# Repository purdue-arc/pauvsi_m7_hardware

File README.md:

# Mission-7-Triggering-System
The system which triggers the ground robots

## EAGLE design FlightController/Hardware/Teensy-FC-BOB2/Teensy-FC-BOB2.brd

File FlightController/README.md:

# Mission-7-Flight-Controller
This repository holds the pcb design and code for the flight controller

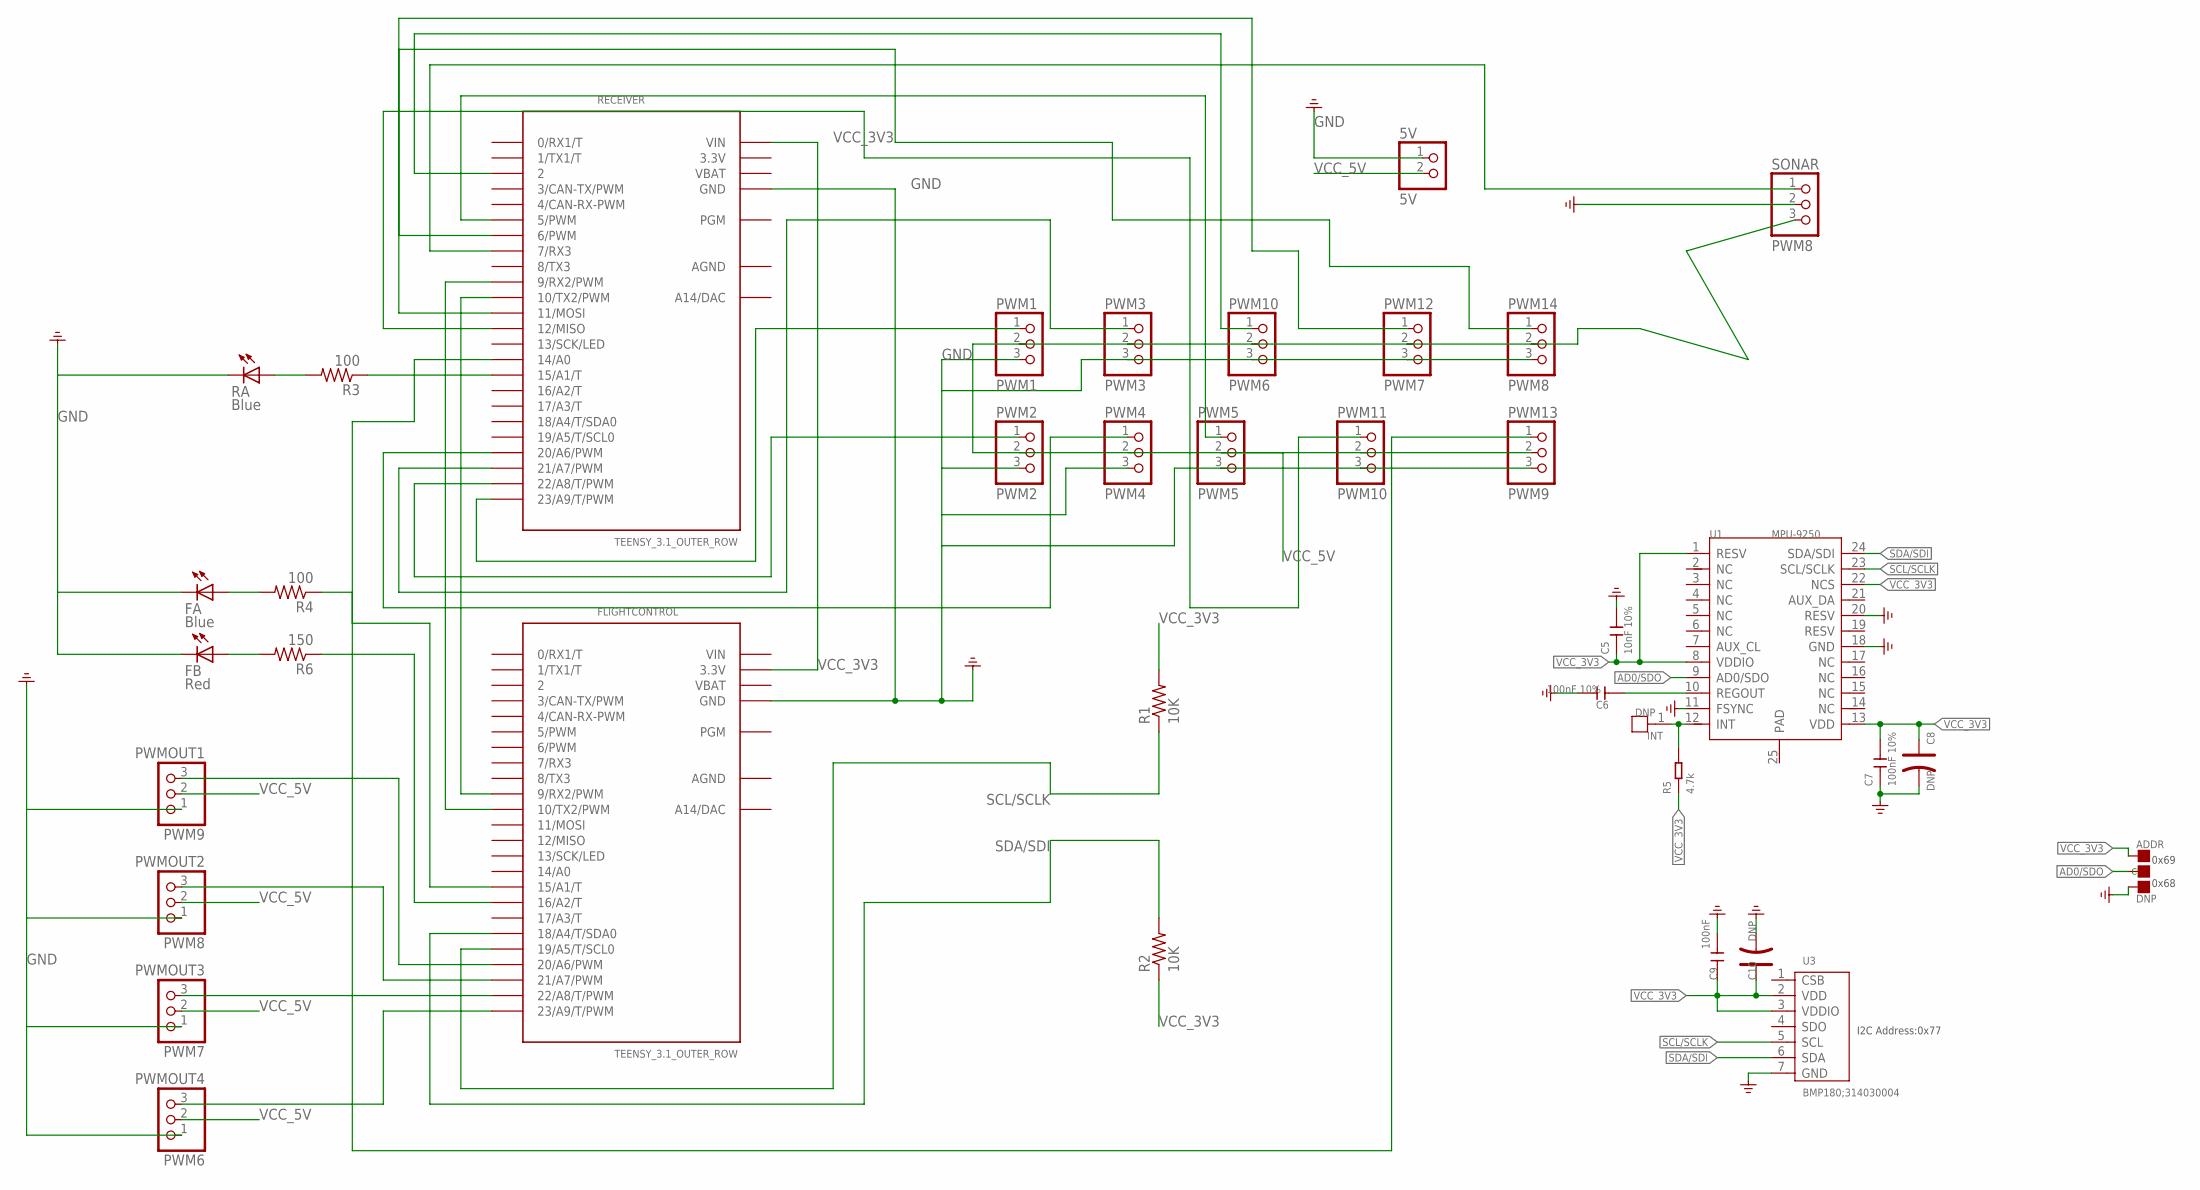
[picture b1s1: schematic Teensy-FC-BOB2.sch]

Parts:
5V: 5V; 1X02
ADDR: DNP; 3P-SMD-L4.1*W1.5MM
C5: 10nF 10%; C0603
C6, C7: 100nF 10%; C0603
C8, C10: DNP; AVX-A
C9: 100nF; C0603
FA: Blue; CHIP-LED0603
FB: Red; CHIP-LED0603
FLIGHTCONTROL: TEENSY_3.1_OUTER_ROW; TEENSY3-OUTER_ROW
INT: DNP; 1P-65/35MIL
PWM1: PWM1; 1X03
PWM2: PWM2; 1X03
PWM3: PWM3; 1X03
PWM4: PWM4; 1X03
PWM5: PWM5; 1X03
PWM6: PWMOUT4; 1X03
PWM7: PWMOUT3; 1X03
PWM8: PWMOUT2; 1X03
PWM9: PWMOUT1; 1X03
PWM10: PWM6; 1X03
PWM11: PWM10; 1X03
PWM12: PWM7; 1X03
PWM13: PWM9; 1X03
PWM14: PWM8; 1X03
R1, R2: 10K; R0603
R3, R4: 100; R0603
R5: 4.7k; R0603
R6: 150; R0603
RA: Blue; CHIP-LED0603
RECEIVER: TEENSY_3.1_OUTER_ROW; TEENSY3-OUTER_ROW
SONAR: PWM8; 1X03
U1: MPU-9250; LEAD-QFN24
U3: BMP180;314030004; LGA-7

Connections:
3.3V: RECEIVER.3.3V, RECEIVER.3.3V1 (3.3V)
AD0/SDO: ADDR.MM (C), U1.9 (AD0/SDO)
AGND: FLIGHTCONTROL.AGND, RECEIVER.AGND
GND: 5V.1, ADDR.11 (R), C5.2, C6.2, C7.1, C8.-, C9.2, C10.-, FA.C, FB.C, FLIGHTCONTROL.GND, FLIGHTCONTROL.GND1 (GND), PWM1.3, PWM2.3, PWM3.3, PWM4.3, PWM5.3, PWM6.1, PWM7.1, PWM8.1, PWM9.1, PWM10.3, PWM11.3, PWM12.3, PWM13.3, PWM14.3, RA.C, RECEIVER.GND, RECEIVER.GND1 (GND), SONAR.2, U1.11 (FSYNC), U1.18 (GND), U1.20 (RESV), U3.7 (GND)
unnamed: FLIGHTCONTROL.9 (9/RX2/PWM), RECEIVER.10 (10/TX2/PWM)
unnamed: FLIGHTCONTROL.10 (10/TX2/PWM), RECEIVER.9 (9/RX2/PWM)
unnamed: C6.1, U1.10 (REGOUT)
unnamed: INT.1, R5.2, U1.12 (INT)
unnamed: PWM1.1, RECEIVER.23/A9 (23/A9/T/PWM)
unnamed: PWM2.1, RECEIVER.22/A8 (22/A8/T/PWM)
unnamed: PWM3.1, RECEIVER.21/A7 (21/A7/PWM)
unnamed: PWM4.1, RECEIVER.20/A6 (20/A6/PWM)
unnamed: PWM5.1, RECEIVER.5 (5/PWM)
unnamed: FLIGHTCONTROL.20/A6 (20/A6/PWM), PWM9.3
unnamed: FLIGHTCONTROL.21/A7 (21/A7/PWM), PWM8.3
unnamed: FLIGHTCONTROL.22/A8 (22/A8/T/PWM), PWM7.3
unnamed: FLIGHTCONTROL.23/A9 (23/A9/T/PWM), PWM6.3
unnamed: FLIGHTCONTROL.15/A1 (15/A1/T), R4.1
unnamed: FA.A, R4.2
unnamed: R3.1, RECEIVER.15/A1 (15/A1/T)
unnamed: R3.2, RA.A
unnamed: FLIGHTCONTROL.16/A2 (16/A2/T), R6.1
unnamed: FB.A, R6.2
unnamed: PWM10.1, RECEIVER.2
unnamed: RECEIVER.7 (7/RX3), SONAR.1
unnamed: PWM1.2, PWM2.2, PWM3.2, PWM4.2, PWM5.2, PWM10.2, PWM11.2, PWM12.2, PWM13.2, PWM14.2, SONAR.3
unnamed: PWM12.1, RECEIVER.6 (6/PWM)
unnamed: PWM14.1, RECEIVER.11 (11/MOSI)
unnamed: PWM11.1, RECEIVER.12 (12/MISO)
unnamed: PWM13.1, RECEIVER.14/A0
SCL/SCLK: FLIGHTCONTROL.19/A5 (19/A5/T/SCL0), R1.1, U1.23 (SCL/SCLK), U3.5 (SCL)
SDA/SDI: FLIGHTCONTROL.18/A4 (18/A4/T/SDA0), R2.2, U1.24 (SDA/SDI), U3.6 (SDA)
VBAT: FLIGHTCONTROL.VBAT, RECEIVER.VBAT
VCC_3V3: ADDR.00 (L), C5.1, C7.2, C8.+, C9.1, C10.+, FLIGHTCONTROL.3.3V, FLIGHTCONTROL.3.3V1 (3.3V), R1.2, R2.1, R5.1, RECEIVER.VIN, U1.1 (RESV), U1.8 (VDDIO), U1.13 (VDD), U1.22 (NCS), U3.2 (VDD), U3.3 (VDDIO)
VCC_5V: 5V.2, PWM6.2, PWM7.2, PWM8.2, PWM9.2
VIN: FLIGHTCONTROL.VIN

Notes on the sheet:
0x69
0x68
I2C Address:0x77

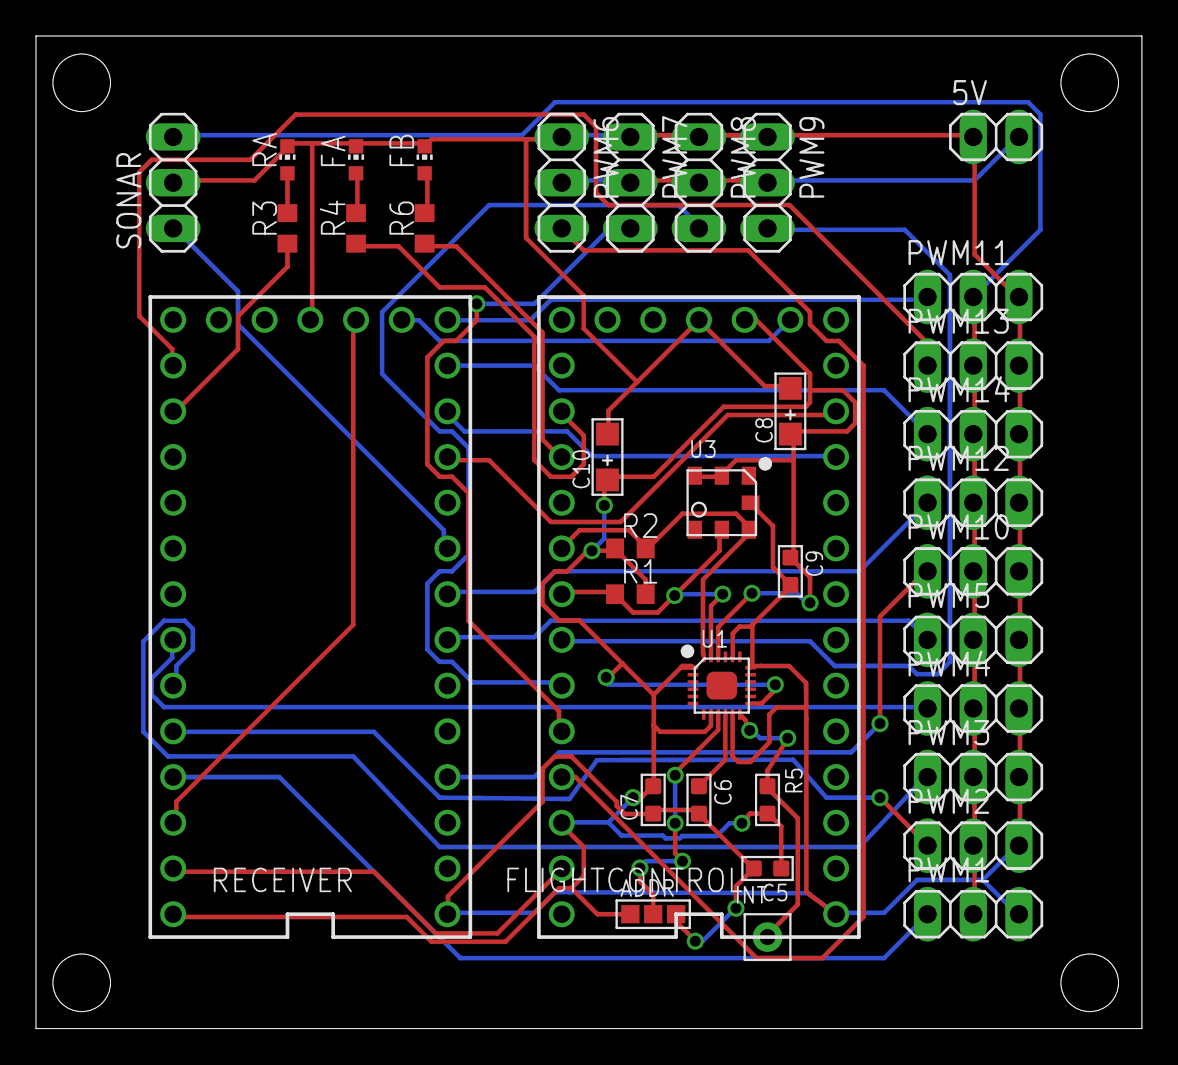
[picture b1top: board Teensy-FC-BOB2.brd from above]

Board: 2 copper layers, 61.4 x 55.1 mm, 37 parts (0 on the bottom side), 35 nets.

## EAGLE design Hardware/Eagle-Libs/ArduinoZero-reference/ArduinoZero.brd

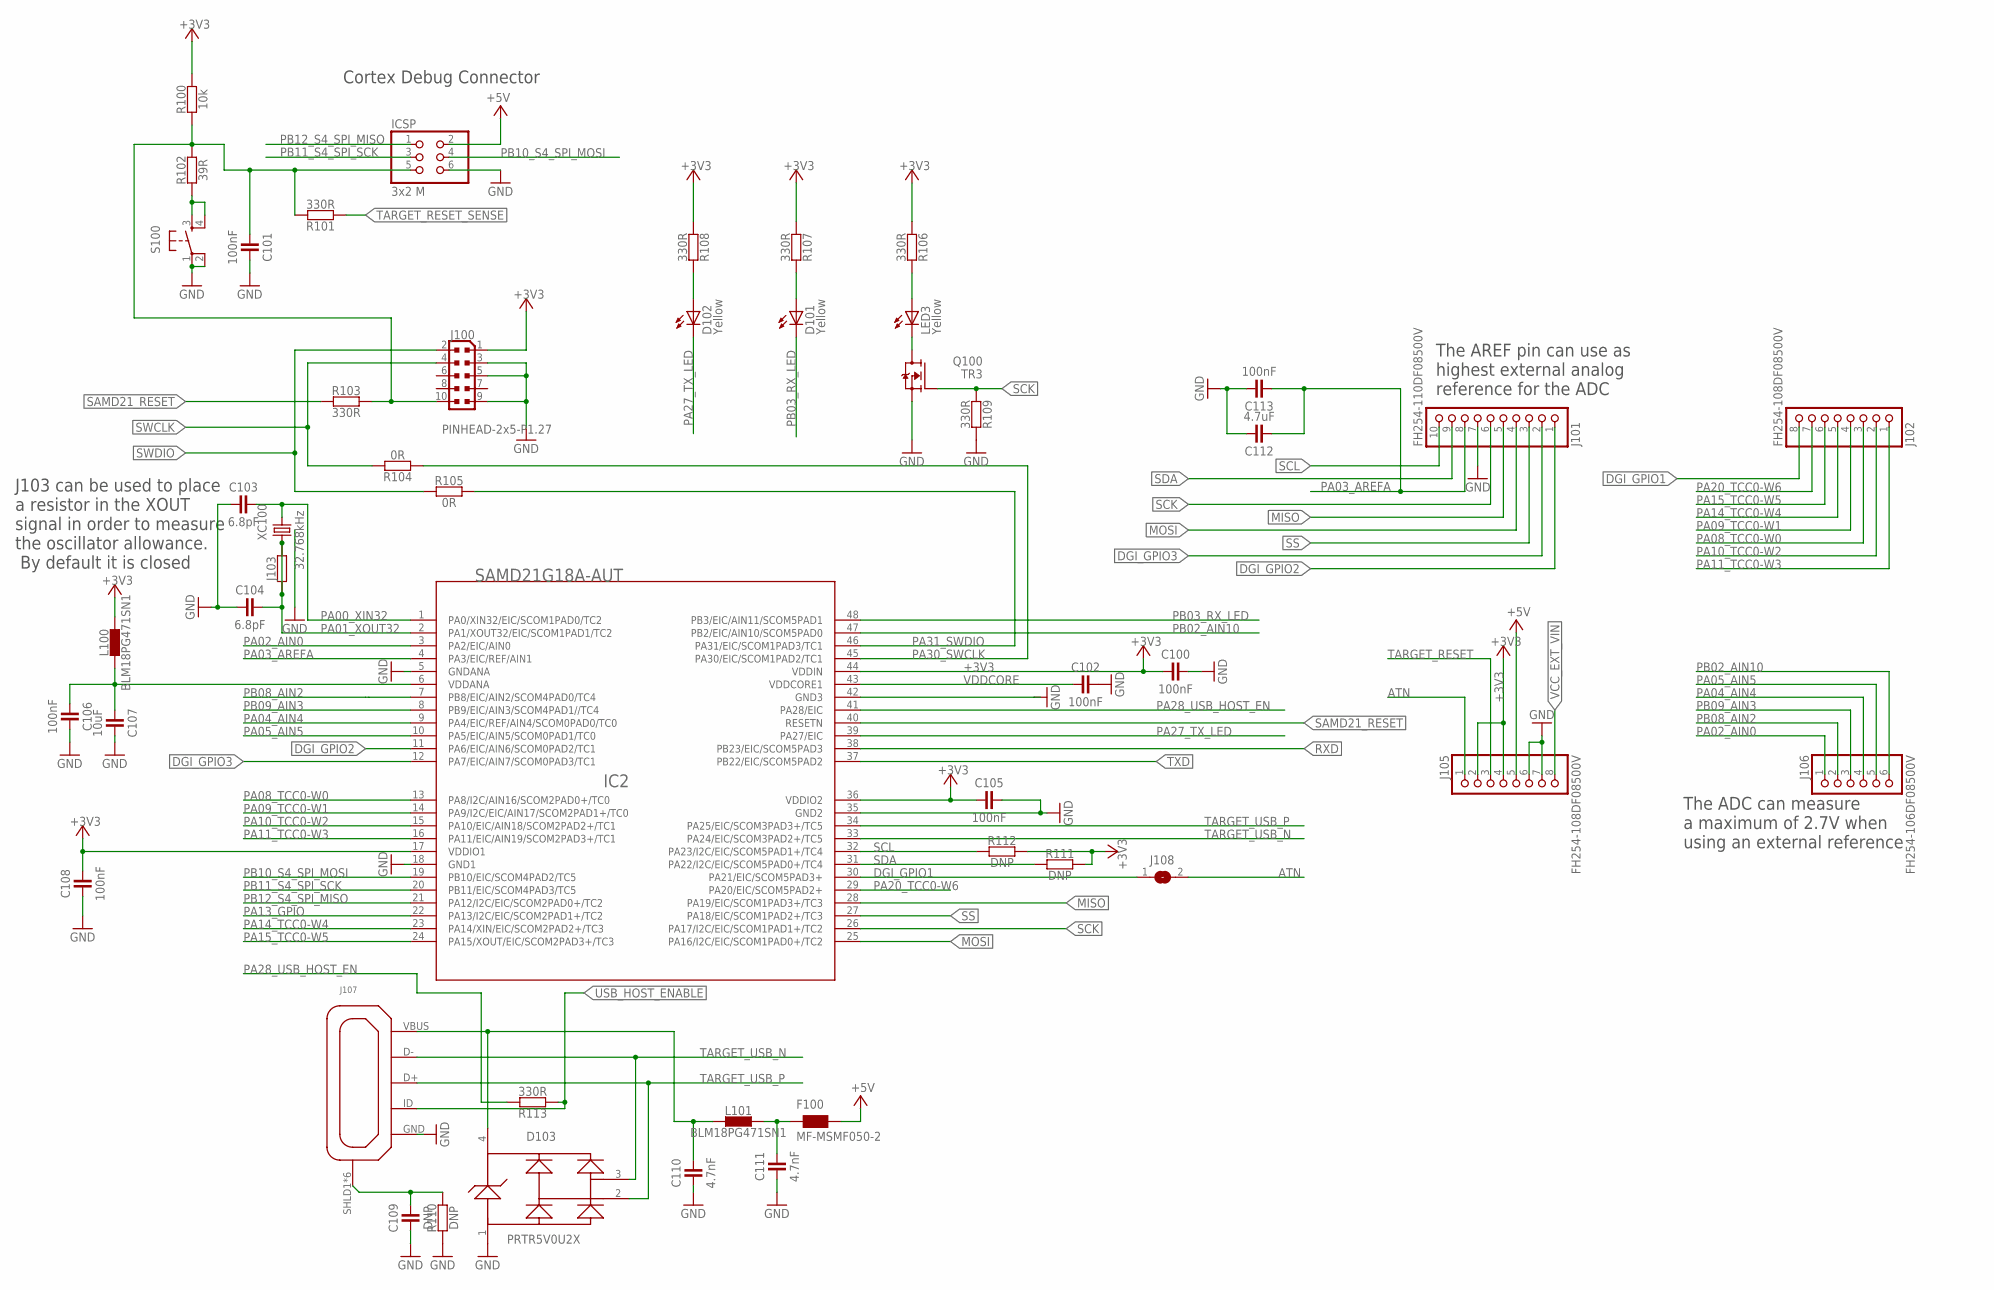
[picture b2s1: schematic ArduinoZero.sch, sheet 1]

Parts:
C100, C101, C102, C105, C106, C108, C113: 100nF; C0402
C103, C104: 6.8pF; C0402
C107: 10uF; C0603
C109: DNP; C0402
C110, C111: 4.7nF; C0402
C112: 4.7uF; C0603
D101, D102: Yellow; CHIPLED_0805
D103: PRTR5V0U2XB; SOT143B
F100: MF-MSMF050-2; WUERTH-ELEKTRONIK_1812
IC2: SAMD21G18A-AUT; TQFP48
ICSP: 3x2 M; 2X03
J100: PINHEAD-2x5-P1.27; PINHEAD_2X05_127
J101: FH254-110DF08500V; 1X10
J102, J105: FH254-108DF08500V; 1X08
J103: RESISTORS-0402; C0402
J106: FH254-106DF08500V; 1X06
J107: ZX62-AB-5PA; USB-MICRO-10103594
J108: SJ
L100, L101: BLM18PG471SN1; C0603
LED3: Yellow; CHIPLED_0805
R100: 10k; C0402
R101, R103, R106, R107, R108, R109, R113: 330R; C0402
R102: 39R; C0402
R104, R105: 0R; C0402
R110, R111, R112: DNP; C0402
S100: PUSHBUTTON3; TS42_4PINS
TR3: Q100; SOT-23
XC100: 32.768kHz; CRYSTAL_TC26SMD

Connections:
+3V3: C100.1, C105.1, C108.2, IC2.17 (VDDIO1), IC2.36 (VDDIO2), IC2.44 (VDDIN), J100.1, J105.2, J105.4, L100.2, R100.2, R106.1, R107.1, R108.1, R111.2, R112.2; also elsewhere on the board
+5V: F100.2, ICSP.2, J105.5; also elsewhere on the board
ATN: J105.1, J108.2
DGI_GPIO1: IC2.30 (PA21/EIC/SCOM5PAD3+), J102.8, J108.1; also elsewhere on the board
DGI_GPIO2: IC2.11 (PA6/EIC/AIN6/SCOM0PAD2/TC1), J101.1; also elsewhere on the board
DGI_GPIO3: IC2.12 (PA7/EIC/AIN7/SCOM0PAD3/TC1), J101.2; also elsewhere on the board
GND: C100.2, C101.2, C102.2, C103.1, C104.1, C105.2, C106.2, C107.2, C108.1, C109.1, C110.1, C111.1, C112.2, C113.2, D103.1, IC2.5 (GNDANA), IC2.18 (GND1), IC2.35 (GND2), IC2.42 (GND3), ICSP.6, J100.3, J100.5, J100.9, J101.7, J105.6, J105.7, J107.GND, R109.2, R110.1, S100.1, S100.2, TR3.2 (S), XC100.P$1 (GND); also elsewhere on the board
MISO: IC2.28 (PA19/EIC/SCOM1PAD3+/TC3), J101.5; also elsewhere on the board
MOSI: IC2.25 (PA16/I2C/EIC/SCOM1PAD0+/TC2), J101.4; also elsewhere on the board
unnamed: LED3.C, TR3.1 (D)
unnamed: R102.1, S100.3, S100.4
unnamed: C110.2, D103.4, J107.VBUS (VUSB), L101.1
unnamed: C106.1, C107.1, IC2.6 (VDDANA), L100.1
unnamed: C109.2, J107.SHLD1 (SH), J107.SHLD2 (SH), J107.SHLD3 (SH), J107.SHLD4 (SH), J107.SHLD5 (SH), J107.SHLD6 (SH), R110.2
unnamed: C111.2, F100.1, L101.2
unnamed: D102.A, R108.2
unnamed: D101.A, R107.2
unnamed: LED3.A, R106.2
PA00_XIN32: C103.2, IC2.1 (PA0/XIN32/EIC/SCOM1PAD0/TC2), XC100.2
PA01_XOUT32: C104.2, IC2.2 (PA1/XOUT32/EIC/SCOM1PAD1/TC2), J103.1, J103.2, XC100.1
PA02_AIN0: IC2.3 (PA2/EIC/AIN0), J106.1
PA03_AREFA: C112.1, C113.1, IC2.4 (PA3/EIC/REF/AIN1), J101.8
PA04_AIN4: IC2.9 (PA4/EIC/REF/AIN4/SCOM0PAD0/TC0), J106.4
PA05_AIN5: IC2.10 (PA5/EIC/AIN5/SCOM0PAD1/TC0), J106.5
PA08_TCC0-W0: IC2.13 (PA8/I2C/AIN16/SCOM2PAD0+/TC0), J102.3
PA09_TCC0-W1: IC2.14 (PA9/I2C/EIC/AIN17/SCOM2PAD1+/TC0), J102.4
PA10_TCC0-W2: IC2.15 (PA10/EIC/AIN18/SCOM2PAD2+/TC1), J102.2
PA11_TCC0-W3: IC2.16 (PA11/EIC/AIN19/SCOM2PAD3+/TC1), J102.1
PA13_GPIO: IC2.22 (PA13/I2C/EIC/SCOM2PAD1+/TC2)
PA14_TCC0-W4: IC2.23 (PA14/XIN/EIC/SCOM2PAD2+/TC3), J102.5
PA15_TCC0-W5: IC2.24 (PA15/XOUT/EIC/SCOM2PAD3+/TC3), J102.6
PA20_TCC0-W6: IC2.29 (PA20/EIC/SCOM5PAD2+), J102.7
PA27_TX_LED: D102.C, IC2.39 (PA27/EIC)
PA28_USB_HOST_EN: IC2.41 (PA28/EIC), R113.2
PA30_SWCLK: IC2.45 (PA30/EIC/SCOM1PAD2/TC1), R104.1
PA31_SWDIO: IC2.46 (PA31/EIC/SCOM1PAD3/TC1), R105.2
PB02_AIN10: IC2.47 (PB2/EIC/AIN10/SCOM5PAD0), J106.6
PB03_RX_LED: D101.C, IC2.48 (PB3/EIC/AIN11/SCOM5PAD1)
PB08_AIN2: IC2.7 (PB8/EIC/AIN2/SCOM4PAD0/TC4), J106.2
PB09_AIN3: IC2.8 (PB9/EIC/AIN3/SCOM4PAD1//TC4), J106.3
PB10_S4_SPI_MOSI: IC2.19 (PB10/EIC/SCOM4PAD2/TC5), ICSP.4
PB11_S4_SPI_SCK: IC2.20 (PB11/EIC/SCOM4PAD3/TC5), ICSP.3
PB12_S4_SPI_MISO: IC2.21 (PA12/I2C/EIC/SCOM2PAD0+/TC2), ICSP.1
RXD: IC2.38 (PB23/EIC/SCOM5PAD3); also elsewhere on the board
SAMD21_RESET: IC2.40 (RESETN), R103.1; also elsewhere on the board
SCK: IC2.26 (PA17/I2C/EIC/SCOM1PAD1+/TC2), J101.6, R109.1, TR3.3 (G); also elsewhere on the board
SCL: IC2.32 (PA23/I2C/EIC/SCOM5PAD1+/TC4), J101.10, R112.1; also elsewhere on the board
SDA: IC2.31 (PA22/I2C/EIC/SCOM5PAD0+/TC4), J101.9, R111.1; also elsewhere on the board
SS: IC2.27 (PA18/EIC/SCOM1PAD2+/TC3), J101.3; also elsewhere on the board
SWCLK: J100.4, R104.2; also elsewhere on the board
SWDIO: J100.2, R105.1; also elsewhere on the board
TARGET_RESET: C101.1, ICSP.5, J100.10, J105.3, R100.1, R101.2, R102.2, R103.2
TARGET_RESET_SENSE: R101.1; also elsewhere on the board
TARGET_USB_N: D103.3, IC2.33 (PA24/EIC/SCOM3PAD2+/TC5), J107.D-
TARGET_USB_P: D103.2, IC2.34 (PA25/EIC/SCOM3PAD3+/TC5), J107.D+
TXD: IC2.37 (PB22/EIC/SCOM5PAD2); also elsewhere on the board
USB_HOST_ENABLE: J107.ID, R113.1; also elsewhere on the board
VCC_EXT_VIN: J105.8; also elsewhere on the board
VDDCORE: C102.1, IC2.43 (VDDCORE1)

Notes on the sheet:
Cortex Debug Connector
J103 can be used to place a resistor in the XOUT signal in order to measure the oscillator allowance. By default it is closed
The ADC can measure a maximum of 2.7V when using an external reference
The AREF pin can use as highest external analog reference for the ADC

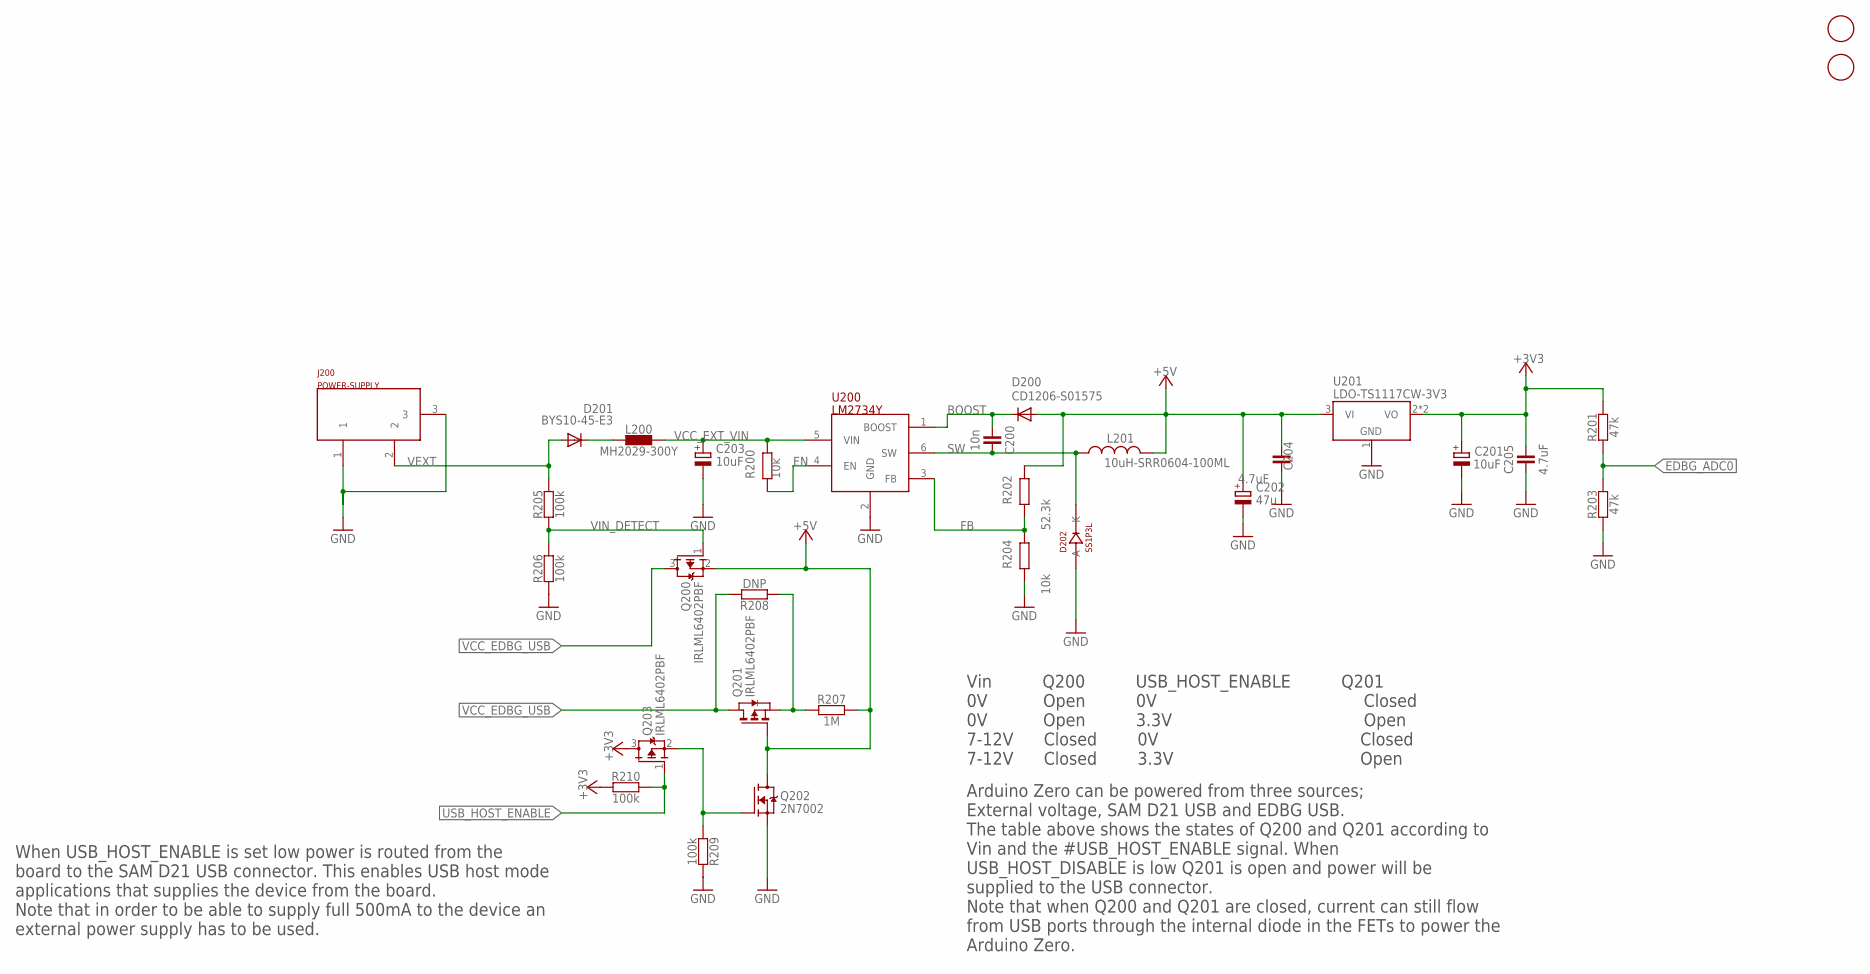
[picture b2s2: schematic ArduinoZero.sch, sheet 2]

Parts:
C200: 10n; C0402
C201, C203: 10uF; PANASONIC_D
C202: 47u; PANASONIC_D
C204, C205: 4.7uF; C0603
D200: CD1206-S01575; MINIMELF
D201: BYS10-45-E3; MINIMELF
D202: SS1P3L; DO220AAL
FD1, FD2: FIDUCIALMOUNT; FIDUCIA-MOUNT
J200: POWER-SUPPLY; POWERSUPPLY_DC-21MM
L200: MH2029-300Y; C0805
L201: 10uH-SRR0604-100ML; SRR0604
Q200, Q203: IRLML6402PBF; SOT323
Q201: IRLML6402PBF; SOT-23
Q202: 2N7002; SOT23
R200, R204: 10k; C0402
R201, R203: 47k; C0402
R202: 52.3k; C0402
R205, R206, R209, R210: 100k; C0402
R207: 1M; C0402
R208: DNP; C0402
U200: LM2734Y; SOT23-6
U201: LDO-TS1117CW-3V3; SOT223

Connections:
+3V3: C201.+, C205.2, Q203.3 (D), R201.2, R210.1, U201.2 (VO), U201.4 (VO); also elsewhere on the board
+5V: C202.+, C204.1, D200.A, L201.P$2 (2), Q200.2 (S), Q201.3 (G), Q202.3 (D), R202.1, R207.2, U201.3 (VI); also elsewhere on the board
BOOST: C200.1, D200.C, U200.1 (BOOST)
EDBG_ADC0: R201.1, R203.2; also elsewhere on the board
EN: R200.2, U200.4 (EN)
FB: R202.2, R204.1, U200.3 (FB)
GND: C201.-, C202.-, C203.-, C204.2, C205.1, D202.P$2 (A), J200.1, J200.3, Q202.2 (S), R203.1, R204.2, R206.1, R209.2, U200.2 (GND), U201.1 (GND); also elsewhere on the board
unnamed: Q201.2 (S), R207.1, R208.1
unnamed: D201.C, L200.1
unnamed: Q202.1 (G), Q203.2 (S), R209.1
SW: C200.2, D202.P$1 (K), L201.P$1 (1), U200.6 (SW)
USB_HOST_ENABLE: Q203.1 (G), R210.2; also elsewhere on the board
VCC_EDBG_USB: Q200.3 (D), Q201.1 (D), R208.2; also elsewhere on the board
VCC_EXT_VIN: C203.+, L200.2, R200.1, U200.5 (VIN); also elsewhere on the board
VEXT: D201.A, J200.2, R205.2
VIN_DETECT: Q200.1 (G), R205.1, R206.2

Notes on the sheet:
Arduino Zero can be powered from three sources; External voltage, SAM D21 USB and EDBG USB. The table above shows the states of Q200 and Q201 according to Vin and the #USB_HOST_ENABLE signal. When USB_HOST_DISABLE is low Q201 is open and power will be supplied to the USB connector. Note that when Q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
Vin Q200 USB_HOST_ENABLE Q201 0V Open 0V Closed 0V Open 3.3V Open 7-12V Closed 0V Closed 7-12V Closed 3.3V Open
When USB_HOST_ENABLE is set low power is routed from the board to the SAM D21 USB connector. This enables USB host mode applications that supplies the device from the board. Note that in order to be able to supply full 500mA to the device an external power supply has to be used.

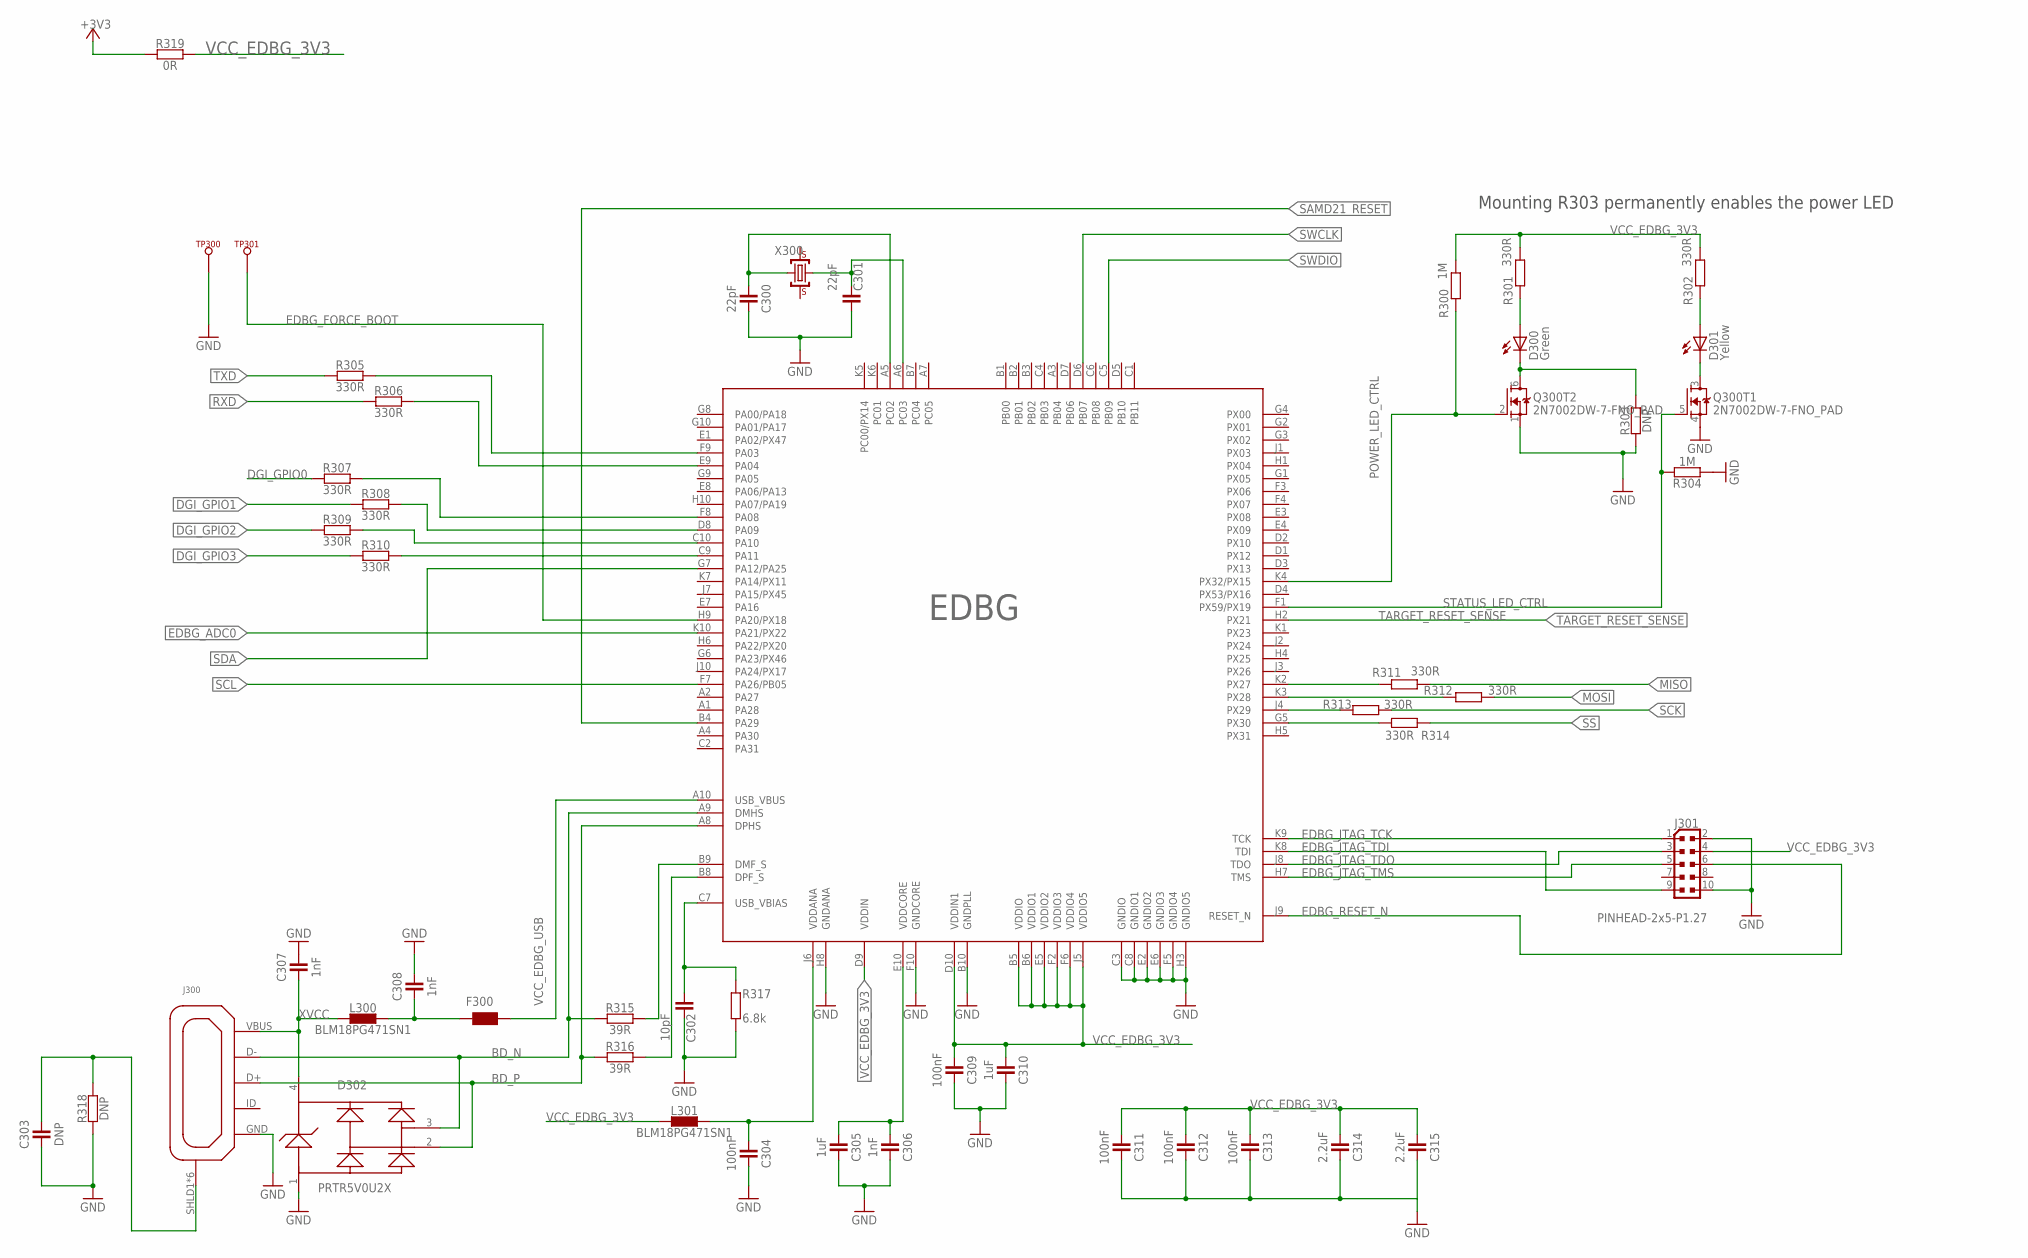
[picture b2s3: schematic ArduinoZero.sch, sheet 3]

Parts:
C300, C301: 22pF; C0402
C302: 10pF; C0402
C303: DNP; C0402
C304, C309, C311, C312, C313: 100nF; C0402
C305, C310: 1uF; C0402
C306, C307, C308: 1nF; C0402
C314, C315: 2.2uF; C0402
D300: Green; CHIPLED_0805
D301: Yellow; CHIPLED_0805
D302: PRTR5V0U2XB; SOT143B
EDBG: EDBG; VFBGA100
F300: WUERTH-ELEKTRONIK_WE-CBF_1812; WUERTH-ELEKTRONIK_1812
J300: ZX62-AB-5PA; USB-MICRO-10103594
J301: PINHEAD-2x5-P1.27; PINHEAD_2X05_127
L300, L301: BLM18PG471SN1; C0603
Q300: 2N7002DW-7-FNO_PAD; PWR_SC70-6L2
R300, R304: 1M; C0402
R301, R302, R305, R306, R307, R308, R309, R310, R311, R312, R313, R314: 330R; C0402
R303, R318: DNP; C0402
R315, R316: 39R; C0402
R317: 6.8k; C0402
R319: 0R; C0402
TP300, TP301: TP_SP; TP-SP
X300: 12mHz-12pF-K7; CRYSTAL-5.4-3.2

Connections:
+3V3: R319.1; also elsewhere on the board
BD_N: D302.3, EDBG.A9 (DMHS), J300.D-, R315.1
BD_P: D302.2, EDBG.A8 (DPHS), J300.D+, R316.1
DGI_GPIO0: R307.1
DGI_GPIO1: R308.1; also elsewhere on the board
DGI_GPIO2: R309.1; also elsewhere on the board
DGI_GPIO3: R310.1; also elsewhere on the board
EDBG_ADC0: EDBG.K10 (PA21/PX22); also elsewhere on the board
EDBG_FORCE_BOOT: EDBG.H9 (PA20/PX18), TP301.X
EDBG_JTAG_TCK: EDBG.K9 (TCK), J301.1
EDBG_JTAG_TDI: EDBG.K8 (TDI), J301.9
EDBG_JTAG_TDO: EDBG.J8 (TDO), J301.3
EDBG_JTAG_TMS: EDBG.H7 (TMS), J301.5
EDBG_RESET_N: EDBG.J9 (RESET_N), J301.6
GND: C300.2, C301.2, C302.2, C303.1, C304.2, C305.2, C306.2, C307.2, C308.2, C309.2, C310.2, C311.2, C312.2, C313.2, C314.2, C315.2, D302.1, EDBG.B10 (GNDPLL), EDBG.C3 (GNDIO), EDBG.C8 (GNDIO1), EDBG.E2 (GNDIO2), EDBG.E6 (GNDIO3), EDBG.F5 (GNDIO4), EDBG.F10 (GNDCORE), EDBG.H3 (GNDIO5), EDBG.H8 (GNDANA), J300.GND, J301.2, J301.10, Q300.1 (S), Q300.4 (S), R303.1, R304.1, R317.1, R318.1, TP300.X; also elsewhere on the board
MISO: R311.2; also elsewhere on the board
MOSI: R312.2; also elsewhere on the board
unnamed: D300.C, Q300.6 (D), R303.2
unnamed: D301.C, Q300.3 (D)
unnamed: C303.2, J300.SHLD1 (SH), J300.SHLD2 (SH), J300.SHLD3 (SH), J300.SHLD4 (SH), J300.SHLD5 (SH), J300.SHLD6 (SH), R318.2
unnamed: C308.1, F300.1, L300.2
unnamed: EDBG.B9 (DMF_S), R315.2
unnamed: EDBG.B8 (DPF_S), R316.2
unnamed: C302.1, EDBG.C7 (USB_VBIAS), R317.2
unnamed: C301.1, EDBG.A6 (PC03), X300.1 (C1)
unnamed: C300.1, EDBG.A5 (PC02), X300.3 (C2)
unnamed: C305.1, C306.1, EDBG.E10 (VDDCORE)
unnamed: C304.1, EDBG.J6 (VDDANA), L301.2
unnamed: EDBG.K2 (PX27), R311.1
unnamed: EDBG.K3 (PX28), R312.1
unnamed: EDBG.J4 (PX29), R313.1
unnamed: EDBG.G5 (PX30), R314.1
unnamed: EDBG.C9 (PA11), R310.2
unnamed: EDBG.C10 (PA10), R309.2
unnamed: EDBG.D8 (PA09), R308.2
unnamed: EDBG.F8 (PA08), R307.2
unnamed: EDBG.E9 (PA04), R306.2
unnamed: EDBG.F9 (PA03), R305.2
unnamed: D300.A, R301.1
unnamed: D301.A, R302.1
POWER_LED_CTRL: EDBG.K4 (PX32/PX15), Q300.2 (G), R300.1
RXD: R306.1; also elsewhere on the board
SAMD21_RESET: EDBG.B4 (PA29); also elsewhere on the board
SCK: R313.2; also elsewhere on the board
SCL: EDBG.F7 (PA26/PB05); also elsewhere on the board
SDA: EDBG.G7 (PA12/PA25); also elsewhere on the board
SS: R314.2; also elsewhere on the board
STATUS_LED_CTRL: EDBG.F1 (PX59/PX19), Q300.5 (G), R304.2
SWCLK: EDBG.D6 (PB07); also elsewhere on the board
SWDIO: EDBG.C5 (PB09); also elsewhere on the board
TARGET_RESET_SENSE: EDBG.H2 (PX21); also elsewhere on the board
TXD: R305.1; also elsewhere on the board
VCC_EDBG_3V3: C309.1, C310.1, C311.1, C312.1, C313.1, C314.1, C315.1, EDBG.B5 (VDDIO), EDBG.B6 (VDDIO1), EDBG.D9 (VDDIN), EDBG.D10 (VDDIN1), EDBG.E5 (VDDIO2), EDBG.F2 (VDDIO3), EDBG.F6 (VDDIO4), EDBG.J5 (VDDIO5), J301.4, L301.1, R300.2, R301.2, R302.2, R319.2
VCC_EDBG_USB: EDBG.A10 (USB_VBUS), F300.2; also elsewhere on the board
XVCC: C307.1, D302.4, J300.VBUS (VUSB), L300.1

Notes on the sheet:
Mounting R303 permanently enables the power LED

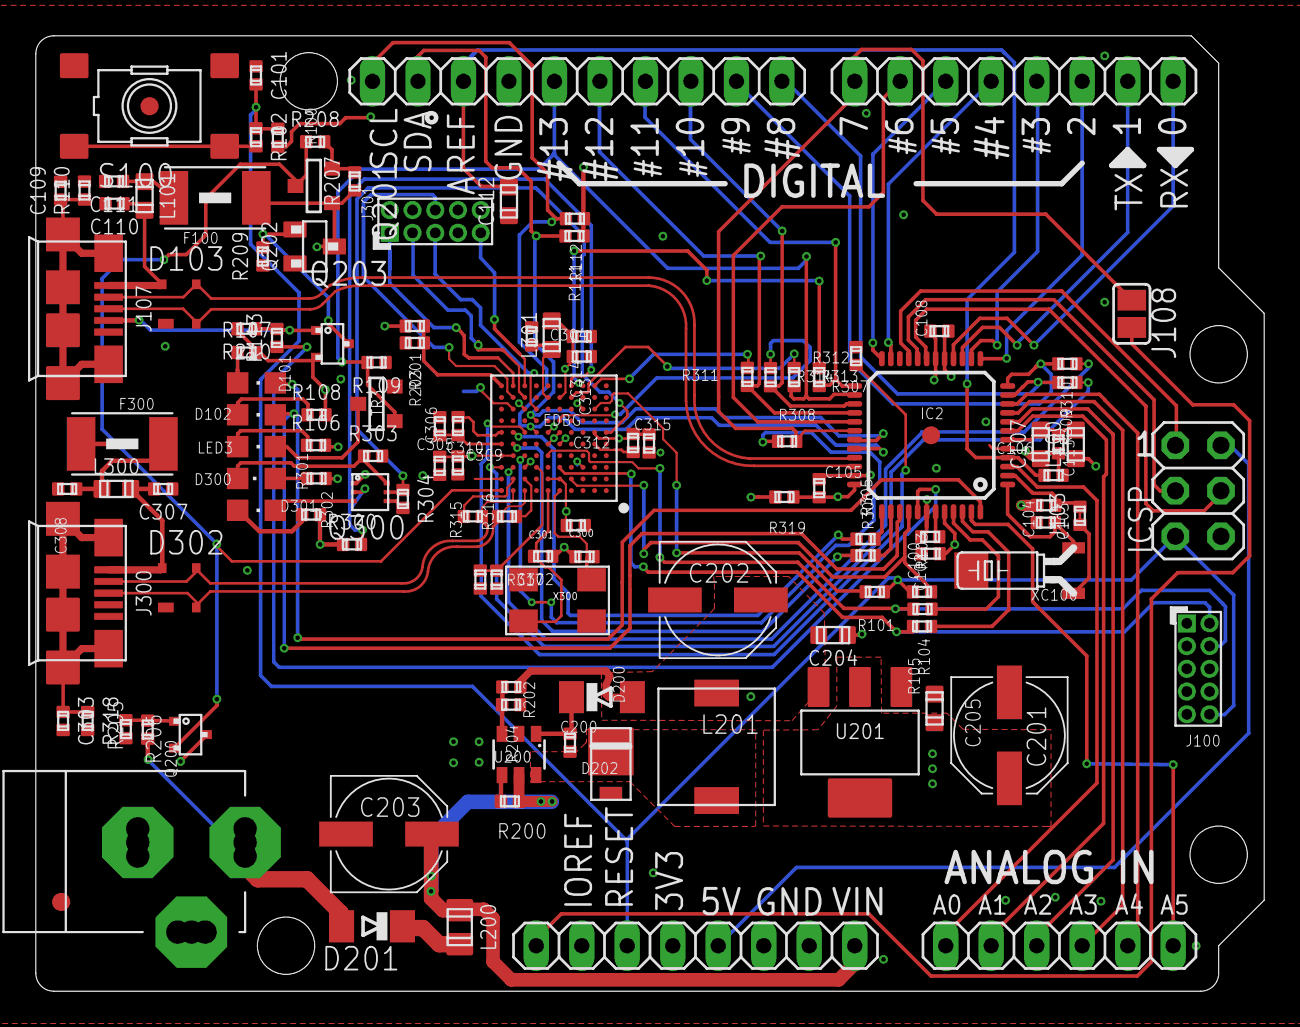
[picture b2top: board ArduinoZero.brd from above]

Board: 4 copper layers, 68.6 x 53.3 mm, 128 parts (0 on the bottom side), 104 nets.

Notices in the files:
parts and their libraries:
con-usb: Copyright (C) 2008, Bob Starr
SparkFun-Electromechanical: Licensing: Creative Commons ShareAlike 4.0 International - https://creativecommons.org/licenses/by-sa/4.0
